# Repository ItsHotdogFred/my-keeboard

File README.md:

# My Keeboard

A custom TKL-inspired keyboard designed around my own setup and workflow.

Originally built for Hack Club's **KEEB** event, the project was later moved over to **Fabricate**.

## Features

- **Two rotary encoders**: one for system volume and one for microphone volume, with press-to-mute for quick mic muting
- **Custom width**: sized to match the armrest of my current keyboard
- **RGB lighting**: because RGB is cool

## Why I Built It

1. **To learn PCB design**: I have never made a PCB before this project and I am happy to say that I have learnt a new skill.
2. **To fit my use case**: I could really use 2 rotary encoders instead of just one.

The case was designed in [Onshape](https://cad.onshape.com/documents/9cc6d087942bd9a75f4ed666/w/a5c6ec7e2ee84bae6976a53f/e/82ebf20b905067d4074dacd5?renderMode=0&uiState=6ae6b1350ce1492784b3f556)

## BOM

| Item | Description | Qty | Unit Price (NZ$) | Line Total (NZ$) | Link |
|---|---|---|---|---|---|
| 10/100M Electrical Tape | Black Rubber Electrical High-Temperature Resistant tape (10M) | 1 | 7.49 | 7.49 | [Link](https://www.aliexpress.com/item/1005009961470227.html) |
| Coiled Keyboard Cable | NNBILI Type C to USB-A Coiled Aviator Keyboard cable | 1 | 14.89 | 14.89 | [Link](https://www.aliexpress.com/item/1005007219379988.html) |
| 100pcs/lot IN4148 | 1N4148 diodes in stock | 1 | 3.69 | 3.69 | [Link](https://www.aliexpress.com/item/4001126137167.html) |
| SK6812 MINI-E LED beads | 50-100Pcs full-color LED beads SK6812 3228 built-in IC | 1 | 14.19 | 14.19  | [Link](https://www.aliexpress.com/item/1005010491444748.html) |
| EC11 rotary encoder | 5PCS EC11 half/plum blossom shaft 15/20mm with switch | 1 | 3.29 | 3.29 | [Link](https://www.aliexpress.com/item/1005008665849783.html) |
| RP2040 dev board | Official Raspberry Pi Pico RP2040 board | 1 | 6.79 | 6.79 | [Link](https://www.aliexpress.com/item/1005006839247100.html) |
| PCB mounted screw-in stabilizers | Original Cherry PCB Stabilizers Satellite Axis 7u 6.25u etc. | 1 | 19.79 | 19.79 | [Link](https://www.aliexpress.com/item/4001143514438.html) |
| RGB backlit keycaps | New Gradient Gray Double Shot OEM Profile 135 Key set | 1 | 22.09 | 22.09 | [Link](https://www.aliexpress.com/item/1005012423299905.html) |
| Outemu mechanical switches | Dust-Proof Brown 90PCS 3Pin (select Brown + 90pcs) | 1 | 31.19 | 31.19 | [Link](https://www.aliexpress.com/item/1005009249474760.html) |
| PCB | PCB for the keyboard | 1 | 47.45 | 47.45 | NO LINK
| **Total** | | | | **169.77** | |

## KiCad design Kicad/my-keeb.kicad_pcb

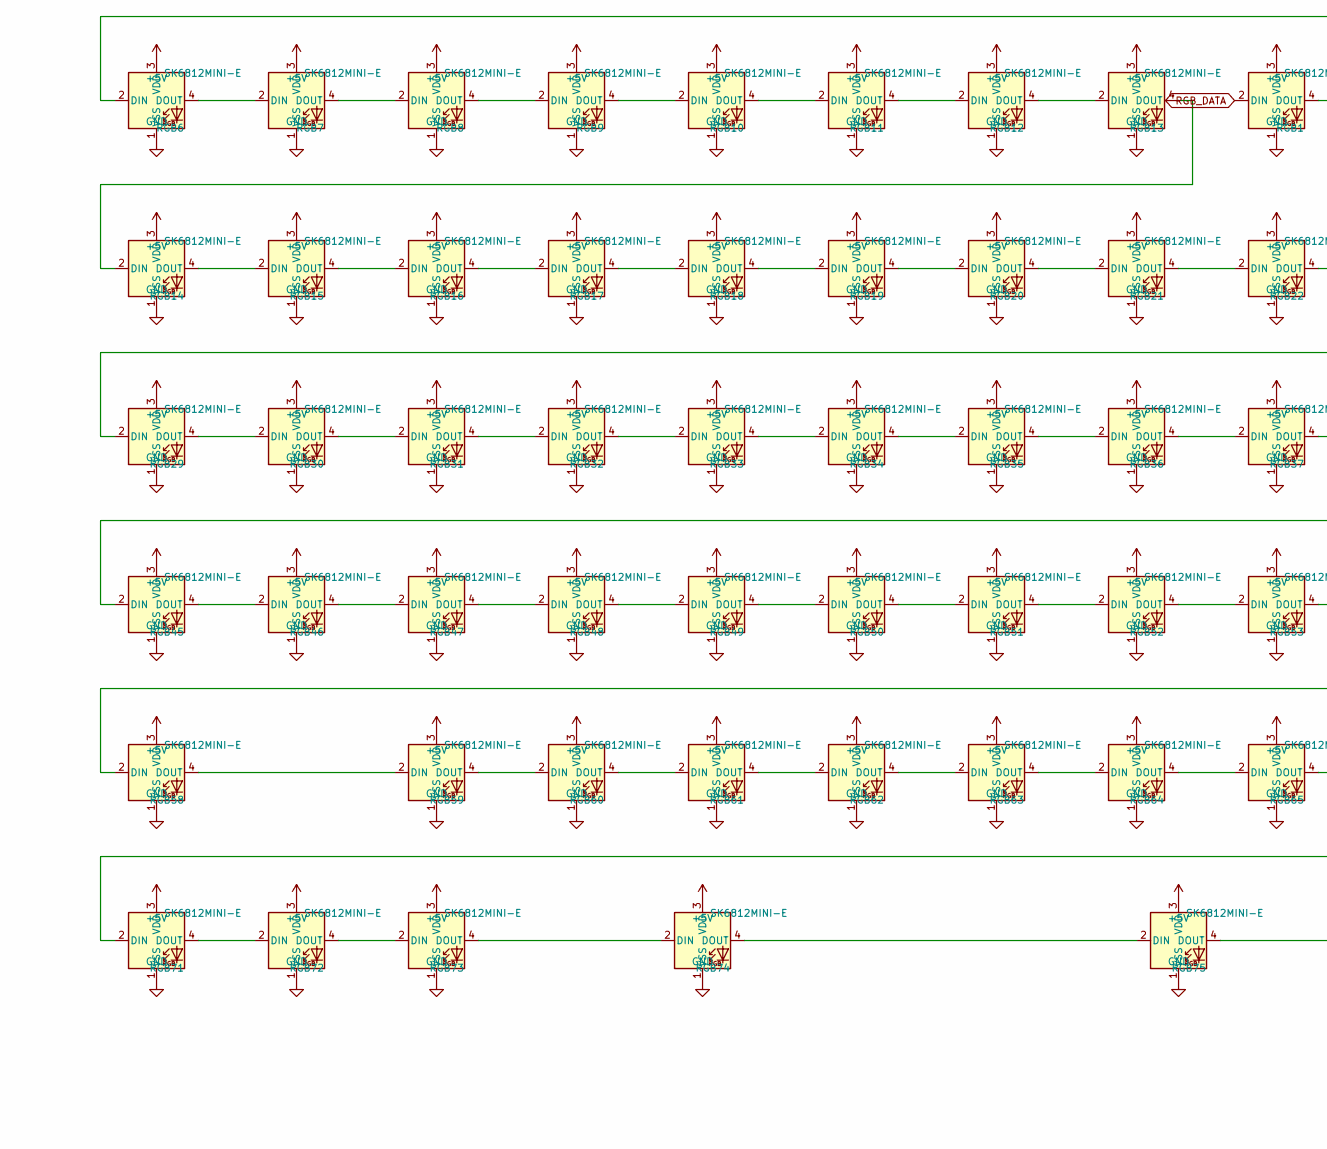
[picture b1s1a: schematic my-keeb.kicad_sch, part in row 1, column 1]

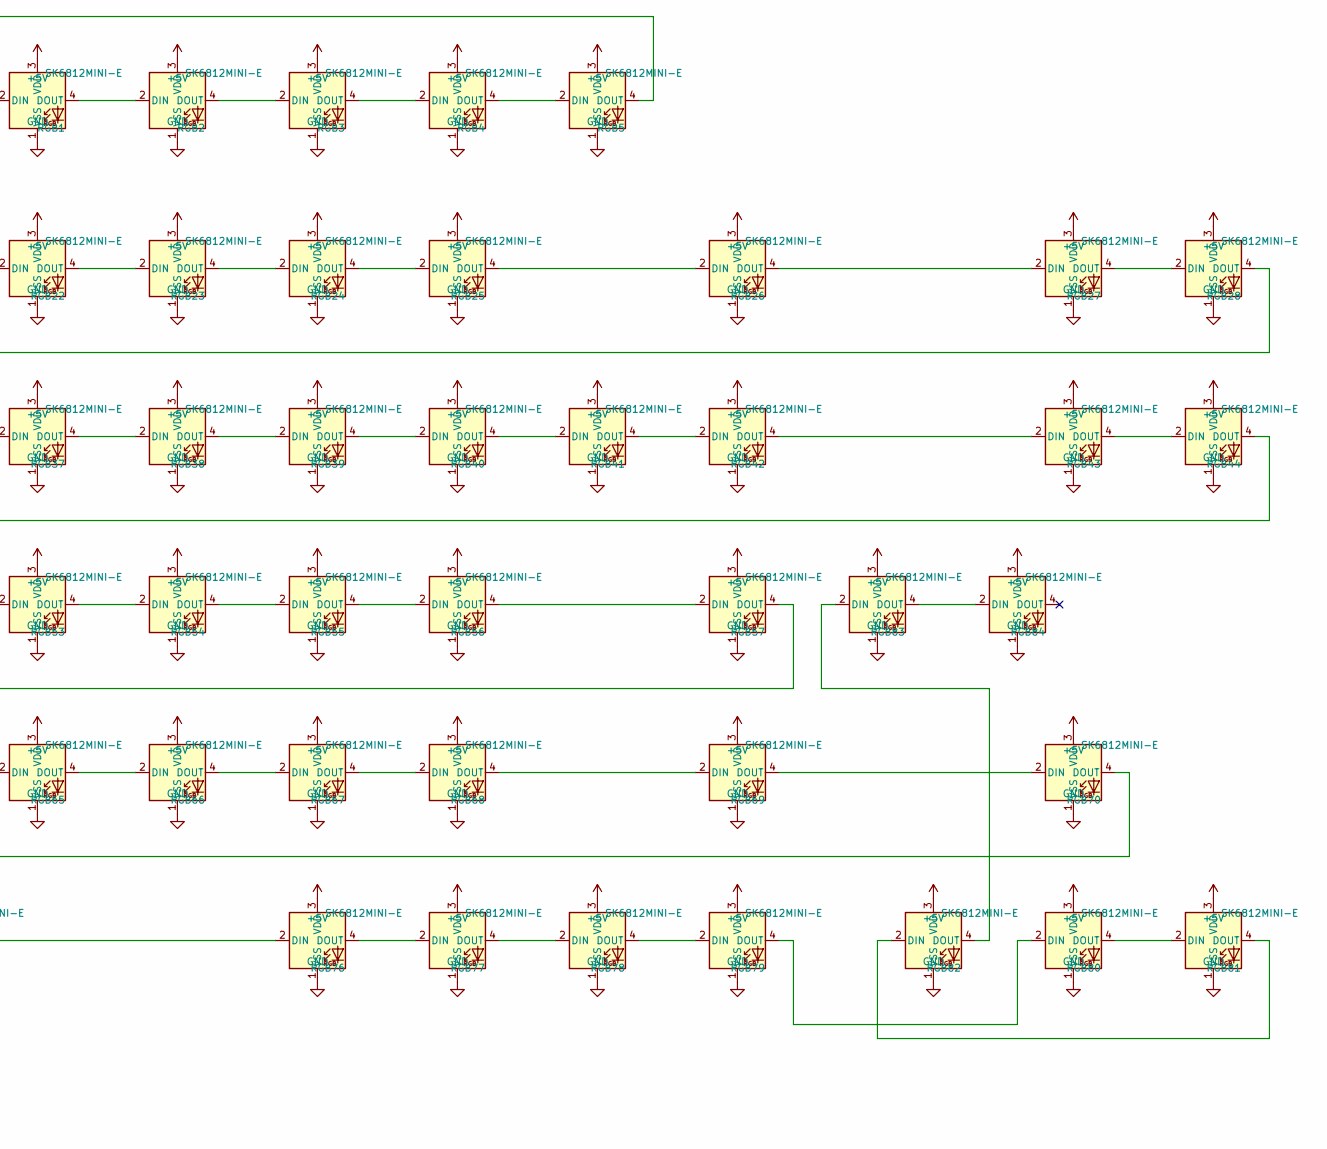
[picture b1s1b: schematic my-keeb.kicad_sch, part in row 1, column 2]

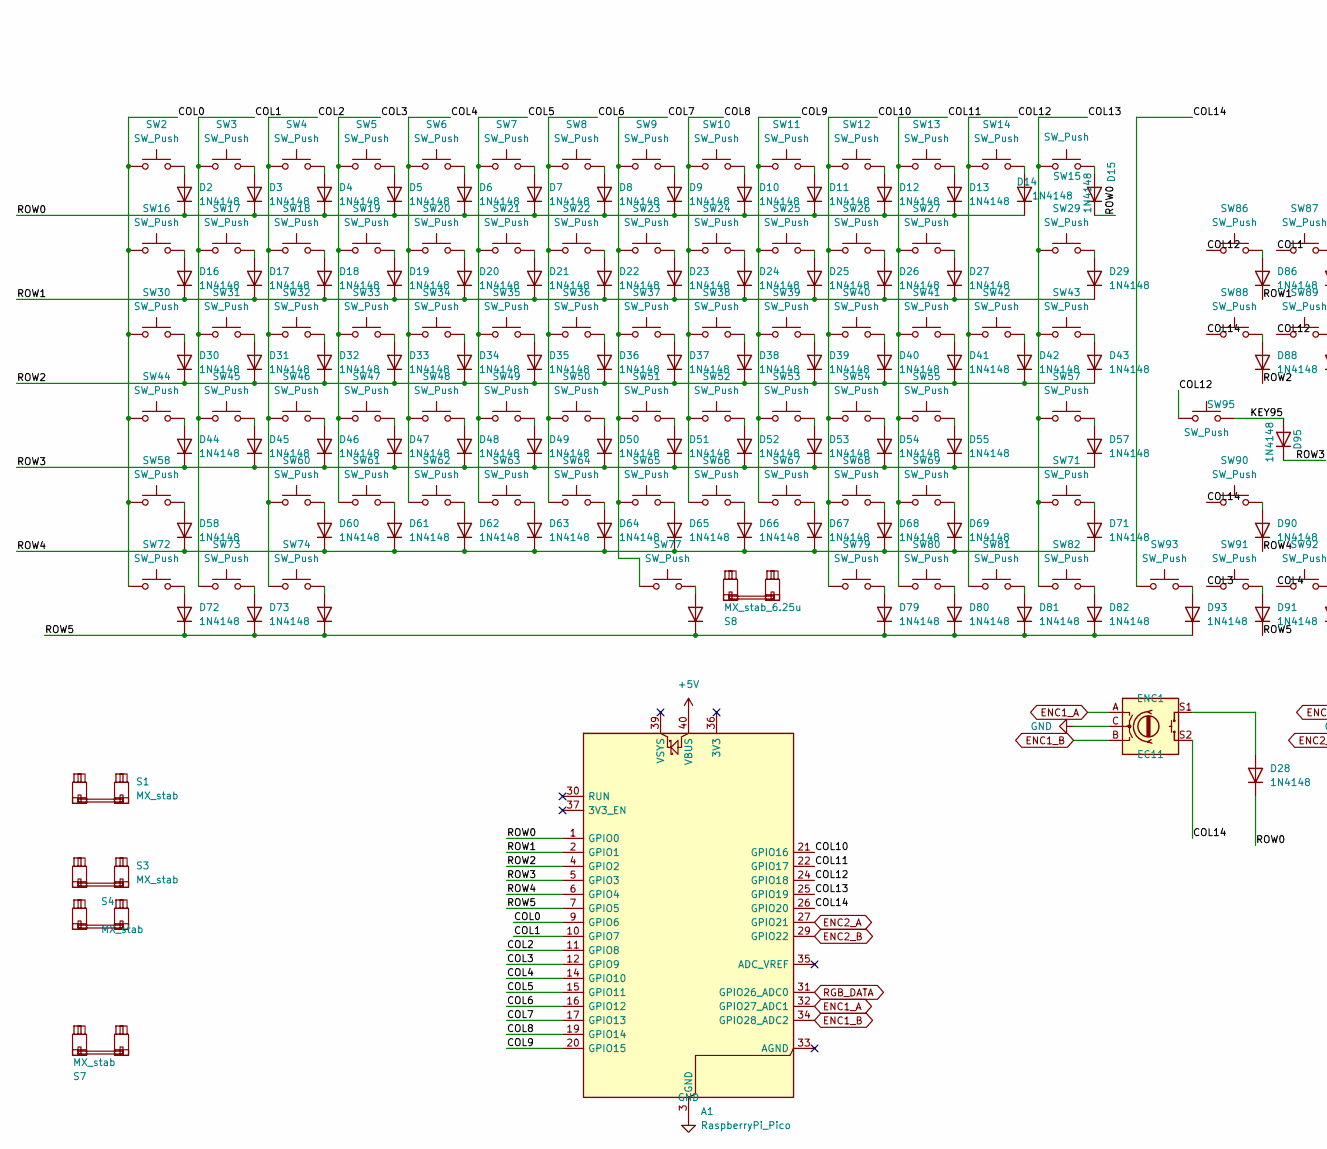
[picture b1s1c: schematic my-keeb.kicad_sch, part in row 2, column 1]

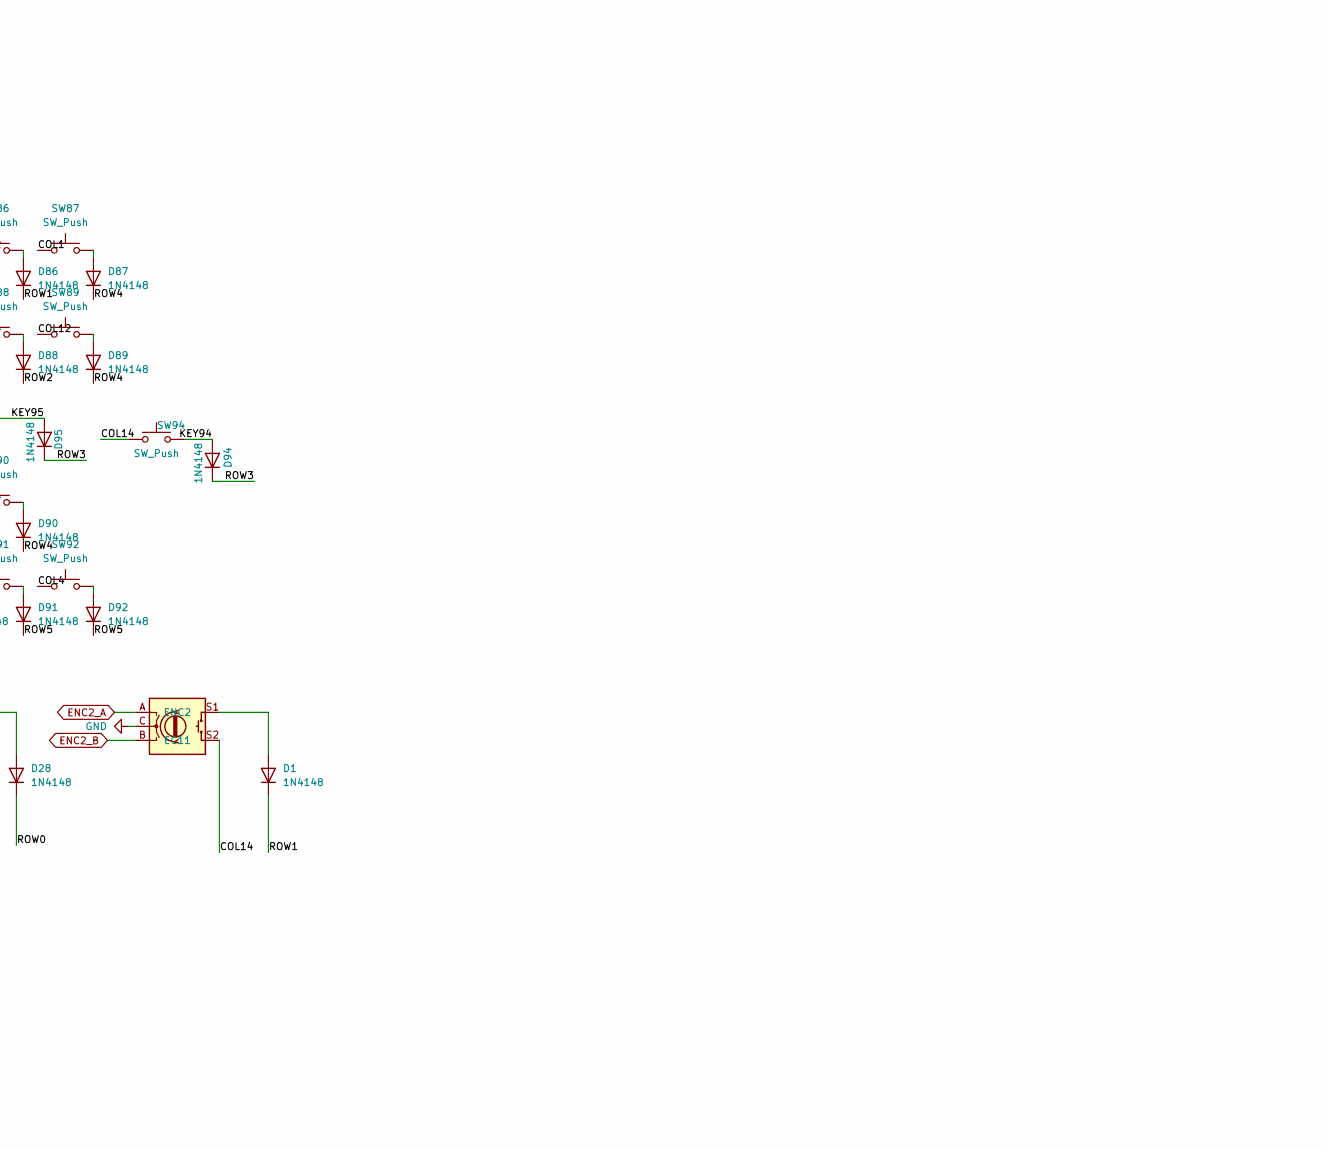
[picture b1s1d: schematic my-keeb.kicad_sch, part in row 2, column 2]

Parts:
A1: RaspberryPi_Pico; RaspberryPi_Pico_Common_THT
D1, D2, D3, D4, D5, D6, D7, D8, D9, D10, D11, D12, D13, D14, D15, D16, D17, D18, D19, D20, D21, D22, D23, D24, D25, D26, D27, D28, D29, D30, D31, D32, D33, D34, D35, D36, D37, D38, D39, D40, D41, D42, D43, D44, D45, D46, D47, D48, D49, D50, D51, D52, D53, D54, D55, D57, D58, D60, D61, D62, D63, D64, D65, D66, D67, D68, D69, D71, D72, D73, D74, D77, D79, D80, D81, D82, D86, D87, D88, D89, D90, D91, D92, D93, D94, D95: 1N4148; D_DO-35_SOD27_P7.62mm_Horizontal
ENC1, ENC2: EC11; RotaryEncoder_Alps_EC11E-Switch_Vertical_H20mm
RGB1, RGB2, RGB3, RGB4, RGB5, RGB6, RGB7, RGB8, RGB9, RGB10, RGB11, RGB12, RGB13, RGB14, RGB15, RGB16, RGB17, RGB18, RGB19, RGB20, RGB21, RGB22, RGB23, RGB24, RGB25, RGB26, RGB27, RGB28, RGB29, RGB30, RGB31, RGB32, RGB33, RGB34, RGB35, RGB36, RGB37, RGB38, RGB39, RGB40, RGB41, RGB42, RGB43, RGB44, RGB45, RGB46, RGB47, RGB48, RGB49, RGB50, RGB51, RGB52, RGB53, RGB54, RGB55, RGB56, RGB57, RGB58, RGB59, RGB60, RGB61, RGB62, RGB63, RGB64, RGB65, RGB66, RGB67, RGB68, RGB69, RGB70, RGB71, RGB72, RGB73, RGB74, RGB75, RGB76, RGB77, RGB78, RGB79, RGB80, RGB81, RGB82, RGB83, RGB84: SK6812MINI-E; LED_SK6812MINI-E_3.2x2.8mm_P1.5mm_ReverseMount
S1, S3, S4, S7: MX_stab; STAB_MX_P_2u
S8: MX_stab_6.25u; STAB_MX_P_6.25u
SW2, SW3, SW4, SW5, SW6, SW7, SW8, SW9, SW10, SW11, SW12, SW13, SW14, SW15, SW16, SW17, SW18, SW19, SW20, SW21, SW22, SW23, SW24, SW25, SW26, SW27, SW29, SW30, SW31, SW32, SW33, SW34, SW35, SW36, SW37, SW38, SW39, SW40, SW41, SW42, SW43, SW44, SW45, SW46, SW47, SW48, SW49, SW50, SW51, SW52, SW53, SW54, SW55, SW57, SW58, SW60, SW61, SW62, SW63, SW64, SW65, SW66, SW67, SW68, SW69, SW71, SW72, SW73, SW74, SW77, SW79, SW80, SW81, SW82, SW86, SW87, SW88, SW89, SW90, SW91, SW92, SW93, SW94, SW95: SW_Push; SW_MX_1u

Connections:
+5V: A1.40 (VBUS), RGB1.3 (VDD), RGB2.3 (VDD), RGB3.3 (VDD), RGB4.3 (VDD), RGB5.3 (VDD), RGB6.3 (VDD), RGB7.3 (VDD), RGB8.3 (VDD), RGB9.3 (VDD), RGB10.3 (VDD), RGB11.3 (VDD), RGB12.3 (VDD), RGB13.3 (VDD), RGB14.3 (VDD), RGB15.3 (VDD), RGB16.3 (VDD), RGB17.3 (VDD), RGB18.3 (VDD), RGB19.3 (VDD), RGB20.3 (VDD), RGB21.3 (VDD), RGB22.3 (VDD), RGB23.3 (VDD), RGB24.3 (VDD), RGB25.3 (VDD), RGB26.3 (VDD), RGB27.3 (VDD), RGB28.3 (VDD), RGB29.3 (VDD), RGB30.3 (VDD), RGB31.3 (VDD), RGB32.3 (VDD), RGB33.3 (VDD), RGB34.3 (VDD), RGB35.3 (VDD), RGB36.3 (VDD), RGB37.3 (VDD), RGB38.3 (VDD), RGB39.3 (VDD), RGB40.3 (VDD), RGB41.3 (VDD), RGB42.3 (VDD), RGB43.3 (VDD), RGB44.3 (VDD), RGB45.3 (VDD), RGB46.3 (VDD), RGB47.3 (VDD), RGB48.3 (VDD), RGB49.3 (VDD), RGB50.3 (VDD), RGB51.3 (VDD), RGB52.3 (VDD), RGB53.3 (VDD), RGB54.3 (VDD), RGB55.3 (VDD), RGB56.3 (VDD), RGB57.3 (VDD), RGB58.3 (VDD), RGB59.3 (VDD), RGB60.3 (VDD), RGB61.3 (VDD), RGB62.3 (VDD), RGB63.3 (VDD), RGB64.3 (VDD), RGB65.3 (VDD), RGB66.3 (VDD), RGB67.3 (VDD), RGB68.3 (VDD), RGB69.3 (VDD), RGB70.3 (VDD), RGB71.3 (VDD), RGB72.3 (VDD), RGB73.3 (VDD), RGB74.3 (VDD), RGB75.3 (VDD), RGB76.3 (VDD), RGB77.3 (VDD), RGB78.3 (VDD), RGB79.3 (VDD), RGB80.3 (VDD), RGB81.3 (VDD), RGB82.3 (VDD), RGB83.3 (VDD), RGB84.3 (VDD)
/COL0: A1.9 (GPIO6), SW2.1, SW16.1, SW30.1, SW44.1, SW58.1, SW72.1
/COL1: A1.10 (GPIO7), SW3.1, SW17.1, SW31.1, SW45.1, SW73.1, SW87.1
/COL2: A1.11 (GPIO8), SW4.1, SW18.1, SW32.1, SW46.1, SW60.1, SW74.1
/COL3: A1.12 (GPIO9), SW5.1, SW19.1, SW33.1, SW47.1, SW61.1, SW91.1
/COL4: A1.14 (GPIO10), SW6.1, SW20.1, SW34.1, SW48.1, SW62.1, SW92.1
/COL5: A1.15 (GPIO11), SW7.1, SW21.1, SW35.1, SW49.1, SW63.1
/COL6: A1.16 (GPIO12), SW8.1, SW22.1, SW36.1, SW50.1, SW64.1
/COL7: A1.17 (GPIO13), SW9.1, SW23.1, SW37.1, SW51.1, SW65.1, SW77.1
/COL8: A1.19 (GPIO14), SW10.1, SW24.1, SW38.1, SW52.1, SW66.1
/COL9: A1.20 (GPIO15), SW11.1, SW25.1, SW39.1, SW53.1, SW67.1
/COL10: A1.21 (GPIO16), SW12.1, SW26.1, SW40.1, SW54.1, SW68.1, SW79.1
/COL11: A1.22 (GPIO17), SW13.1, SW27.1, SW41.1, SW55.1, SW69.1, SW80.1
/COL12: A1.24 (GPIO18), SW14.1, SW42.1, SW81.1, SW86.1, SW89.1, SW95.1
/COL13: A1.25 (GPIO19), SW15.1, SW29.1, SW43.1, SW57.1, SW71.1, SW82.1
/COL14: A1.26 (GPIO20), ENC1.S2, ENC2.S2, SW88.1, SW90.1, SW93.1, SW94.1
/KEY94: D94.2 (A), SW94.2
/KEY95: D95.2 (A), SW95.2
/ROW0: A1.1 (GPIO0), D2.1 (K), D3.1 (K), D4.1 (K), D5.1 (K), D6.1 (K), D7.1 (K), D8.1 (K), D9.1 (K), D10.1 (K), D11.1 (K), D12.1 (K), D13.1 (K), D14.1 (K), D15.1 (K), D28.1 (K)
/ROW1: A1.2 (GPIO1), D1.1 (K), D16.1 (K), D17.1 (K), D18.1 (K), D19.1 (K), D20.1 (K), D21.1 (K), D22.1 (K), D23.1 (K), D24.1 (K), D25.1 (K), D26.1 (K), D27.1 (K), D29.1 (K), D86.1 (K)
/ROW2: A1.4 (GPIO2), D30.1 (K), D31.1 (K), D32.1 (K), D33.1 (K), D34.1 (K), D35.1 (K), D36.1 (K), D37.1 (K), D38.1 (K), D39.1 (K), D40.1 (K), D41.1 (K), D42.1 (K), D43.1 (K), D88.1 (K)
/ROW3: A1.5 (GPIO3), D44.1 (K), D45.1 (K), D46.1 (K), D47.1 (K), D48.1 (K), D49.1 (K), D50.1 (K), D51.1 (K), D52.1 (K), D53.1 (K), D54.1 (K), D55.1 (K), D57.1 (K), D94.1 (K), D95.1 (K)
/ROW4: A1.6 (GPIO4), D58.1 (K), D60.1 (K), D61.1 (K), D62.1 (K), D63.1 (K), D64.1 (K), D65.1 (K), D66.1 (K), D67.1 (K), D68.1 (K), D69.1 (K), D71.1 (K), D87.1 (K), D89.1 (K), D90.1 (K)
/ROW5: A1.7 (GPIO5), D72.1 (K), D73.1 (K), D74.1 (K), D77.1 (K), D79.1 (K), D80.1 (K), D81.1 (K), D82.1 (K), D91.1 (K), D92.1 (K), D93.1 (K)
ENC1_A: A1.32 (GPIO27_ADC1), ENC1.A
ENC1_B: A1.34 (GPIO28_ADC2), ENC1.B
ENC2_A: A1.27 (GPIO21), ENC2.A
ENC2_B: A1.29 (GPIO22), ENC2.B
GND: A1.3 (GND), A1.8 (GND), A1.13 (GND), A1.18 (GND), A1.23 (GND), A1.28 (GND), A1.38 (GND), ENC1.C, ENC2.C, RGB1.1 (VSS), RGB2.1 (VSS), RGB3.1 (VSS), RGB4.1 (VSS), RGB5.1 (VSS), RGB6.1 (VSS), RGB7.1 (VSS), RGB8.1 (VSS), RGB9.1 (VSS), RGB10.1 (VSS), RGB11.1 (VSS), RGB12.1 (VSS), RGB13.1 (VSS), RGB14.1 (VSS), RGB15.1 (VSS), RGB16.1 (VSS), RGB17.1 (VSS), RGB18.1 (VSS), RGB19.1 (VSS), RGB20.1 (VSS), RGB21.1 (VSS), RGB22.1 (VSS), RGB23.1 (VSS), RGB24.1 (VSS), RGB25.1 (VSS), RGB26.1 (VSS), RGB27.1 (VSS), RGB28.1 (VSS), RGB29.1 (VSS), RGB30.1 (VSS), RGB31.1 (VSS), RGB32.1 (VSS), RGB33.1 (VSS), RGB34.1 (VSS), RGB35.1 (VSS), RGB36.1 (VSS), RGB37.1 (VSS), RGB38.1 (VSS), RGB39.1 (VSS), RGB40.1 (VSS), RGB41.1 (VSS), RGB42.1 (VSS), RGB43.1 (VSS), RGB44.1 (VSS), RGB45.1 (VSS), RGB46.1 (VSS), RGB47.1 (VSS), RGB48.1 (VSS), RGB49.1 (VSS), RGB50.1 (VSS), RGB51.1 (VSS), RGB52.1 (VSS), RGB53.1 (VSS), RGB54.1 (VSS), RGB55.1 (VSS), RGB56.1 (VSS), RGB57.1 (VSS), RGB58.1 (VSS), RGB59.1 (VSS), RGB60.1 (VSS), RGB61.1 (VSS), RGB62.1 (VSS), RGB63.1 (VSS), RGB64.1 (VSS), RGB65.1 (VSS), RGB66.1 (VSS), RGB67.1 (VSS), RGB68.1 (VSS), RGB69.1 (VSS), RGB70.1 (VSS), RGB71.1 (VSS), RGB72.1 (VSS), RGB73.1 (VSS), RGB74.1 (VSS), RGB75.1 (VSS), RGB76.1 (VSS), RGB77.1 (VSS), RGB78.1 (VSS), RGB79.1 (VSS), RGB80.1 (VSS), RGB81.1 (VSS), RGB82.1 (VSS), RGB83.1 (VSS), RGB84.1 (VSS)
unnamed: D1.2 (A), ENC2.S1
unnamed: D2.2 (A), SW2.2
unnamed: D3.2 (A), SW3.2
unnamed: D4.2 (A), SW4.2
unnamed: D5.2 (A), SW5.2
unnamed: D6.2 (A), SW6.2
unnamed: D7.2 (A), SW7.2
unnamed: D8.2 (A), SW8.2
unnamed: D9.2 (A), SW9.2
unnamed: D10.2 (A), SW10.2
unnamed: D11.2 (A), SW11.2
unnamed: D12.2 (A), SW12.2
unnamed: D13.2 (A), SW13.2
unnamed: D14.2 (A), SW14.2
unnamed: D15.2 (A), SW15.2
unnamed: D16.2 (A), SW16.2
unnamed: D17.2 (A), SW17.2
unnamed: D18.2 (A), SW18.2
unnamed: D19.2 (A), SW19.2
unnamed: D20.2 (A), SW20.2
unnamed: D21.2 (A), SW21.2
unnamed: D22.2 (A), SW22.2
unnamed: D23.2 (A), SW23.2
unnamed: D24.2 (A), SW24.2
unnamed: D25.2 (A), SW25.2
unnamed: D26.2 (A), SW26.2
unnamed: D27.2 (A), SW27.2
unnamed: D28.2 (A), ENC1.S1
unnamed: D29.2 (A), SW29.2
unnamed: D30.2 (A), SW30.2
unnamed: D31.2 (A), SW31.2
unnamed: D32.2 (A), SW32.2
unnamed: D33.2 (A), SW33.2
unnamed: D34.2 (A), SW34.2
unnamed: D35.2 (A), SW35.2
unnamed: D36.2 (A), SW36.2
unnamed: D37.2 (A), SW37.2
unnamed: D38.2 (A), SW38.2
unnamed: D39.2 (A), SW39.2
unnamed: D40.2 (A), SW40.2
unnamed: D41.2 (A), SW41.2
unnamed: D42.2 (A), SW42.2
unnamed: D43.2 (A), SW43.2
unnamed: D44.2 (A), SW44.2
unnamed: D45.2 (A), SW45.2
unnamed: D46.2 (A), SW46.2
unnamed: D47.2 (A), SW47.2
unnamed: D48.2 (A), SW48.2
unnamed: D49.2 (A), SW49.2
unnamed: D50.2 (A), SW50.2
unnamed: D51.2 (A), SW51.2
unnamed: D52.2 (A), SW52.2
unnamed: D53.2 (A), SW53.2
unnamed: D54.2 (A), SW54.2
unnamed: D55.2 (A), SW55.2
unnamed: D57.2 (A), SW57.2
unnamed: D58.2 (A), SW58.2
unnamed: D60.2 (A), SW60.2
unnamed: D61.2 (A), SW61.2
unnamed: D62.2 (A), SW62.2
unnamed: D63.2 (A), SW63.2
unnamed: D64.2 (A), SW64.2
unnamed: D65.2 (A), SW65.2
unnamed: D66.2 (A), SW66.2
unnamed: D67.2 (A), SW67.2
unnamed: D68.2 (A), SW68.2
unnamed: D69.2 (A), SW69.2
unnamed: D71.2 (A), SW71.2
unnamed: D72.2 (A), SW72.2
unnamed: D73.2 (A), SW73.2
unnamed: D74.2 (A), SW74.2
unnamed: D77.2 (A), SW77.2
unnamed: D79.2 (A), SW79.2
unnamed: D80.2 (A), SW80.2
unnamed: D81.2 (A), SW81.2
unnamed: D82.2 (A), SW82.2
unnamed: D86.2 (A), SW86.2
unnamed: D87.2 (A), SW87.2
unnamed: D88.2 (A), SW88.2
unnamed: D89.2 (A), SW89.2
unnamed: D90.2 (A), SW90.2
unnamed: D91.2 (A), SW91.2
unnamed: D92.2 (A), SW92.2
unnamed: D93.2 (A), SW93.2
RGB_D1: RGB1.4 (DOUT), RGB2.2 (DIN)
RGB_D2: RGB2.4 (DOUT), RGB3.2 (DIN)
RGB_D3: RGB3.4 (DOUT), RGB4.2 (DIN)
RGB_D4: RGB4.4 (DOUT), RGB5.2 (DIN)
RGB_D5: RGB5.4 (DOUT), RGB6.2 (DIN)
RGB_D6: RGB6.4 (DOUT), RGB7.2 (DIN)
RGB_D7: RGB7.4 (DOUT), RGB8.2 (DIN)
RGB_D8: RGB8.4 (DOUT), RGB9.2 (DIN)
RGB_D9: RGB9.4 (DOUT), RGB10.2 (DIN)
RGB_D10: RGB10.4 (DOUT), RGB11.2 (DIN)
RGB_D11: RGB11.4 (DOUT), RGB12.2 (DIN)
RGB_D12: RGB12.4 (DOUT), RGB13.2 (DIN)
RGB_D13: RGB13.4 (DOUT), RGB14.2 (DIN)
RGB_D14: RGB14.4 (DOUT), RGB15.2 (DIN)
RGB_D15: RGB15.4 (DOUT), RGB16.2 (DIN)
RGB_D16: RGB16.4 (DOUT), RGB17.2 (DIN)
RGB_D17: RGB17.4 (DOUT), RGB18.2 (DIN)
RGB_D18: RGB18.4 (DOUT), RGB19.2 (DIN)
RGB_D19: RGB19.4 (DOUT), RGB20.2 (DIN)
RGB_D20: RGB20.4 (DOUT), RGB21.2 (DIN)
RGB_D21: RGB21.4 (DOUT), RGB22.2 (DIN)
RGB_D22: RGB22.4 (DOUT), RGB23.2 (DIN)
RGB_D23: RGB23.4 (DOUT), RGB24.2 (DIN)
RGB_D24: RGB24.4 (DOUT), RGB25.2 (DIN)
RGB_D25: RGB25.4 (DOUT), RGB26.2 (DIN)
RGB_D26: RGB26.4 (DOUT), RGB27.2 (DIN)
RGB_D27: RGB27.4 (DOUT), RGB28.2 (DIN)
RGB_D28: RGB28.4 (DOUT), RGB29.2 (DIN)
RGB_D29: RGB29.4 (DOUT), RGB30.2 (DIN)
RGB_D30: RGB30.4 (DOUT), RGB31.2 (DIN)
RGB_D31: RGB31.4 (DOUT), RGB32.2 (DIN)
RGB_D32: RGB32.4 (DOUT), RGB33.2 (DIN)
RGB_D33: RGB33.4 (DOUT), RGB34.2 (DIN)
RGB_D34: RGB34.4 (DOUT), RGB35.2 (DIN)
RGB_D35: RGB35.4 (DOUT), RGB36.2 (DIN)
RGB_D36: RGB36.4 (DOUT), RGB37.2 (DIN)
RGB_D37: RGB37.4 (DOUT), RGB38.2 (DIN)
RGB_D38: RGB38.4 (DOUT), RGB39.2 (DIN)
RGB_D39: RGB39.4 (DOUT), RGB40.2 (DIN)
RGB_D40: RGB40.4 (DOUT), RGB41.2 (DIN)
RGB_D41: RGB41.4 (DOUT), RGB42.2 (DIN)
RGB_D42: RGB42.4 (DOUT), RGB43.2 (DIN)
RGB_D43: RGB43.4 (DOUT), RGB44.2 (DIN)
RGB_D44: RGB44.4 (DOUT), RGB45.2 (DIN)
RGB_D45: RGB45.4 (DOUT), RGB46.2 (DIN)
RGB_D46: RGB46.4 (DOUT), RGB47.2 (DIN)
RGB_D47: RGB47.4 (DOUT), RGB48.2 (DIN)
RGB_D48: RGB48.4 (DOUT), RGB49.2 (DIN)
RGB_D49: RGB49.4 (DOUT), RGB50.2 (DIN)
RGB_D50: RGB50.4 (DOUT), RGB51.2 (DIN)
RGB_D51: RGB51.4 (DOUT), RGB52.2 (DIN)
RGB_D52: RGB52.4 (DOUT), RGB53.2 (DIN)
RGB_D53: RGB53.4 (DOUT), RGB54.2 (DIN)
RGB_D54: RGB54.4 (DOUT), RGB55.2 (DIN)
RGB_D55: RGB55.4 (DOUT), RGB56.2 (DIN)
RGB_D56: RGB56.4 (DOUT), RGB57.2 (DIN)
RGB_D57: RGB57.4 (DOUT), RGB58.2 (DIN)
RGB_D58: RGB58.4 (DOUT), RGB59.2 (DIN)
RGB_D59: RGB59.4 (DOUT), RGB60.2 (DIN)
RGB_D60: RGB60.4 (DOUT), RGB61.2 (DIN)
RGB_D61: RGB61.4 (DOUT), RGB62.2 (DIN)
RGB_D62: RGB62.4 (DOUT), RGB63.2 (DIN)
RGB_D63: RGB63.4 (DOUT), RGB64.2 (DIN)
RGB_D64: RGB64.4 (DOUT), RGB65.2 (DIN)
RGB_D65: RGB65.4 (DOUT), RGB66.2 (DIN)
RGB_D66: RGB66.4 (DOUT), RGB67.2 (DIN)
RGB_D67: RGB67.4 (DOUT), RGB68.2 (DIN)
RGB_D68: RGB68.4 (DOUT), RGB69.2 (DIN)
RGB_D69: RGB69.4 (DOUT), RGB70.2 (DIN)
RGB_D70: RGB70.4 (DOUT), RGB71.2 (DIN)
RGB_D71: RGB71.4 (DOUT), RGB72.2 (DIN)
RGB_D72: RGB72.4 (DOUT), RGB73.2 (DIN)
RGB_D73: RGB73.4 (DOUT), RGB74.2 (DIN)
RGB_D74: RGB74.4 (DOUT), RGB75.2 (DIN)
RGB_D75: RGB75.4 (DOUT), RGB76.2 (DIN)
RGB_D76: RGB76.4 (DOUT), RGB77.2 (DIN)
RGB_D77: RGB77.4 (DOUT), RGB78.2 (DIN)
RGB_D78: RGB78.4 (DOUT), RGB79.2 (DIN)
RGB_D79: RGB79.4 (DOUT), RGB80.2 (DIN)
RGB_D80: RGB80.4 (DOUT), RGB81.2 (DIN)
RGB_D81: RGB81.4 (DOUT), RGB82.2 (DIN)
RGB_D82: RGB82.4 (DOUT), RGB83.2 (DIN)
RGB_D83: RGB83.4 (DOUT), RGB84.2 (DIN)
RGB_DATA: A1.31 (GPIO26_ADC0), RGB1.2 (DIN)

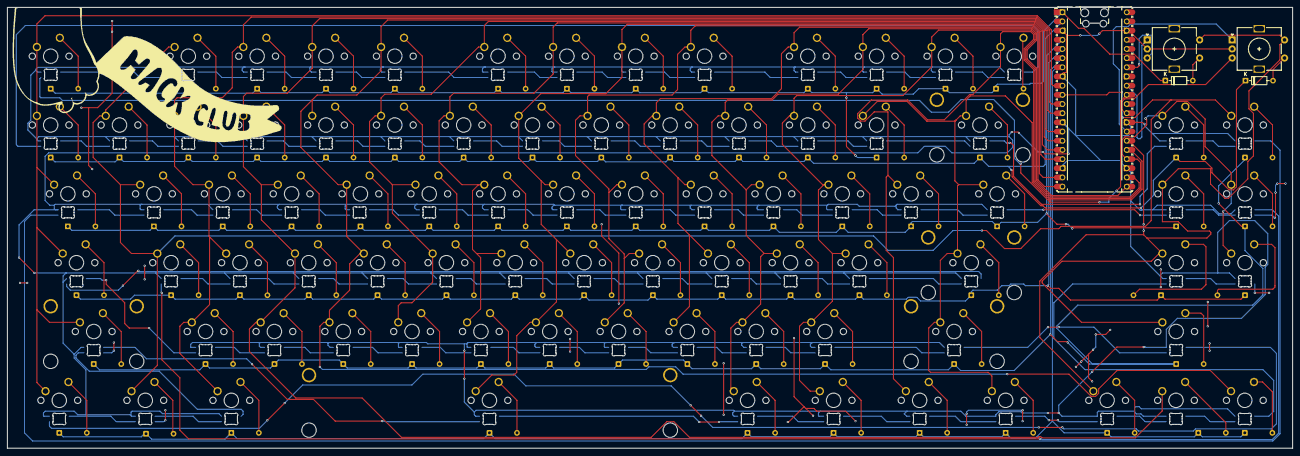
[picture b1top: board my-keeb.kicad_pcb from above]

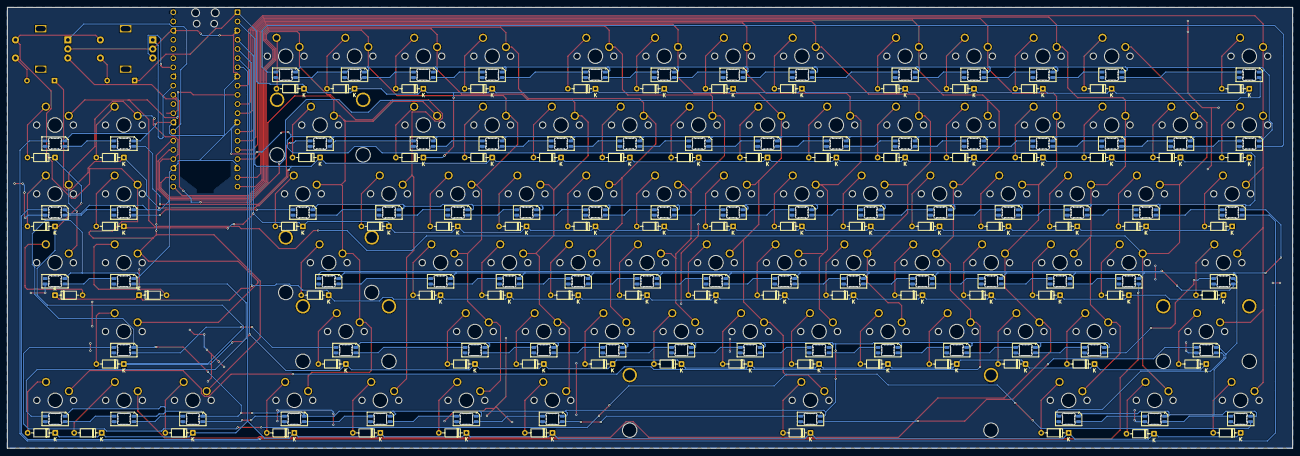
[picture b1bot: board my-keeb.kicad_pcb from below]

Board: 2 copper layers, 355.7 x 122.0 mm, 262 parts (168 on the bottom side), 197 nets.

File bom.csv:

"Reference","Value","Footprint","Datasheet"
"A1","RaspberryPi_Pico","Module:RaspberryPi_Pico_Common_THT","https://datasheets.raspberrypi.com/pico/pico-datasheet.pdf"
"D2,D3,D4,D5,D6,D7,D8,D9,D10,D11,D12,D13,D14,D15,D16,D17,D18,D19,D20,D21,D22,D23,D24,D25,D26,D27,D29,D30,D31,D32,D33,D34,D35,D36,D37,D38,D39,D40,D41,D42,D43,D44,D45,D46,D47,D48,D49,D50,D51,D52,D53,D54,D55,D57,D58,D60,D61,D62,D63,D64,D65,D66,D67,D68,D69,D71,D72,D73,D74,D75,D77,D79,D80,D81,D82,D86,D87,D88,D89,D90,D91,D92,D93,D94,D95","1N4148","Diode_THT:D_DO-35_SOD27_P7.62mm_Horizontal","https://assets.nexperia.com/documents/data-sheet/1N4148_1N4448.pdf"
"ENC1,ENC2","EC11","Rotary_Encoder:RotaryEncoder_Alps_EC11E-Switch_Vertical_H20mm",""
"RGB1,RGB2,RGB3,RGB4,RGB5,RGB6,RGB7,RGB8,RGB9,RGB10,RGB11,RGB12,RGB13,RGB14,RGB15,RGB16,RGB17,RGB18,RGB19,RGB20,RGB21,RGB22,RGB23,RGB24,RGB25,RGB26,RGB27,RGB28,RGB29,RGB30,RGB31,RGB32,RGB33,RGB34,RGB35,RGB36,RGB37,RGB38,RGB39,RGB40,RGB41,RGB42,RGB43,RGB44,RGB45,RGB46,RGB47,RGB48,RGB49,RGB50,RGB51,RGB52,RGB53,RGB54,RGB55,RGB56,RGB57,RGB58,RGB59,RGB60,RGB61,RGB62,RGB63,RGB64,RGB65,RGB66,RGB67,RGB68,RGB69,RGB70,RGB71,RGB72,RGB73,RGB74,RGB75,RGB76,RGB77,RGB78,RGB79,RGB80,RGB81,RGB82,RGB83,RGB84","SK6812MINI-E","LED_SMD:LED_SK6812MINI-E_3.2x2.8mm_P1.5mm_ReverseMount,my-keeb:LED_SK6812MINI-E_3.2x2.8mm_P1.5mm_ReverseMount","https://www.lcsc.com/datasheet/C5149201.pdf"
"S1,S2,S3,S4,S5,S6,S7","MX_stab","my-keeb:STAB_MX_P_2u",""
"SW2,SW3,SW4,SW5,SW6,SW7,SW8,SW9,SW10,SW11,SW12,SW13,SW14,SW16,SW17,SW18,SW19,SW20,SW21,SW22,SW23,SW24,SW25,SW26,SW27,SW29,SW30,SW31,SW32,SW33,SW34,SW35,SW36,SW37,SW38,SW39,SW40,SW41,SW42,SW43,SW44,SW45,SW46,SW47,SW48,SW49,SW50,SW51,SW52,SW53,SW54,SW55,SW57,SW58,SW60,SW61,SW62,SW63,SW64,SW65,SW66,SW67,SW68,SW69,SW71,SW72,SW73,SW74,SW75,SW77,SW79,SW80,SW81,SW82,SW86,SW87,SW88,SW89,SW90,SW91,SW92,SW93,SW94,SW95","SW_Push","PCM_marbastlib-mx:SW_MX_1u",""
